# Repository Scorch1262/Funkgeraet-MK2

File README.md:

# Funkgeraet-MK2

Status:				Unfertig

Bezeichnung:			Funkgerät MK2

Auftragsnummer:			

Auftraggeber:			Privat

Designer:			Torben Bott

Beschreibung:			Funkgerät

				- Qi-Akku-Ladetechnik
				
				- ESP32 Steuerchip mit Bluetooth und WLAN
				
				- passend für DRA818U / DRA818V

Letzte Änderung:		10.05.2019	

Versorgungsspannung (Normal):	5V

Versorgungsspannung (Min.):	

Versorgungsspannung (Max.):	

Interne Spannungen:		5V / 3,7V

Frequenz: 			

Prozessor:			ESP32

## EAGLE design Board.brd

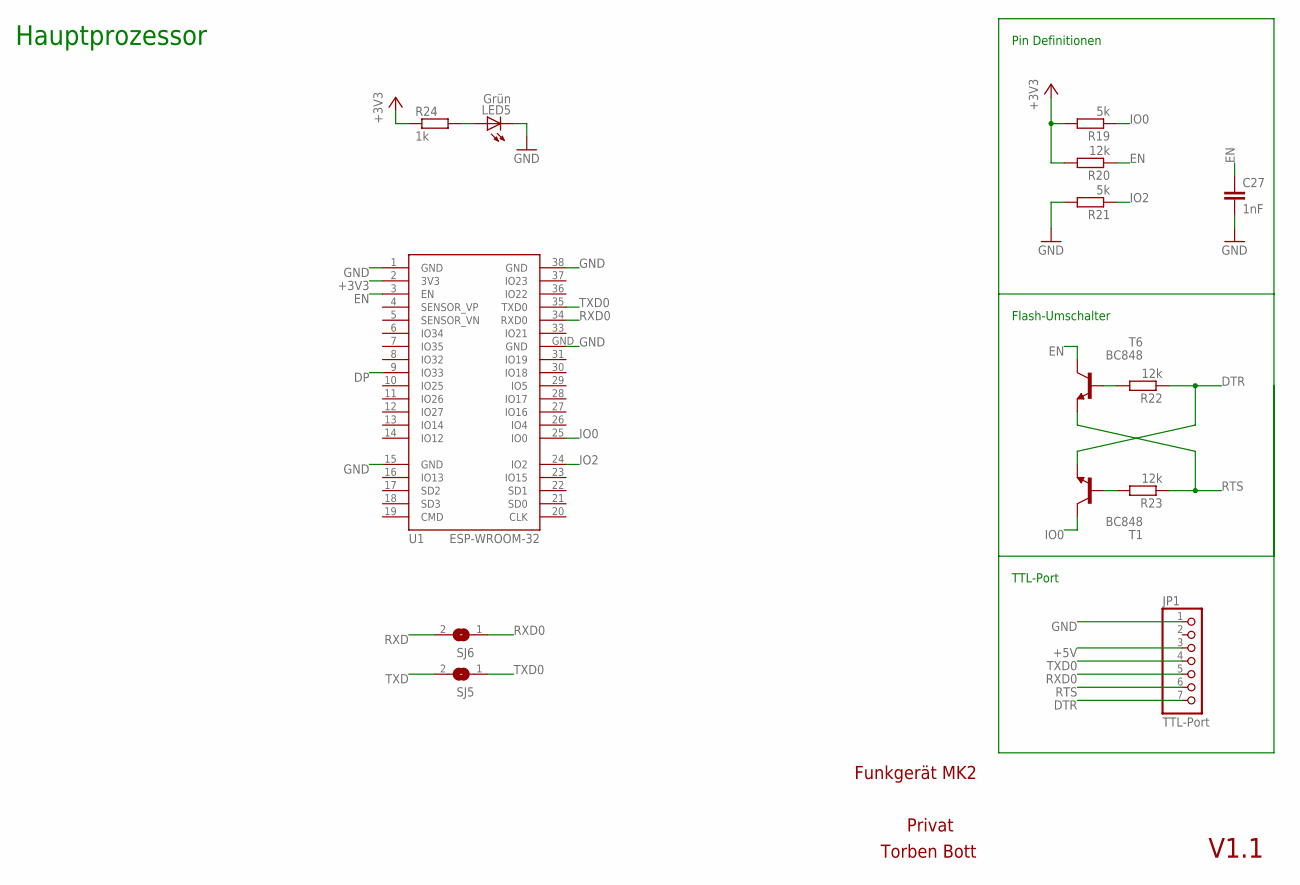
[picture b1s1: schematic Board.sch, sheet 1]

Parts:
C27: 1nF; C0805
JP1: TTL-Port; 1X07/90
LED5: Grün; CHIP-LED0805
R19, R21: 5k; R0805
R20, R22, R23: 12k; R0805
R24: 1k; R0805
SJ5, SJ6: SJ
T1, T6: BC848; SOT23
U1: ESP-WROOM-32

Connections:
+3V3: R19.2, R20.2, R24.1, U1.2 (3V3); also elsewhere on the board
+5V: JP1.3; also elsewhere on the board
DP: U1.9 (IO33); also elsewhere on the board
DTR: JP1.7, R22.1, T1.2 (E)
EN: C27.1, R20.1, T6.3 (C), U1.3 (EN)
GND: C27.2, JP1.1, LED5.C, R21.2, U1.1 (GND), U1.15 (GND), U1.38 (GND), U1.GND; also elsewhere on the board
IO0: R19.1, T1.3 (C), U1.25 (IO0)
IO2: R21.1, U1.24 (IO2)
unnamed: R23.2, T1.1 (B)
unnamed: R22.2, T6.1 (B)
unnamed: LED5.A, R24.2
RTS: JP1.6, R23.1, T6.2 (E)
RXD: SJ6.2; also elsewhere on the board
RXD0: JP1.5, SJ6.1, U1.34 (RXD0)
TXD: SJ5.2; also elsewhere on the board
TXD0: JP1.4, SJ5.1, U1.35 (TXD0)

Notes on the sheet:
Pin Definitionen
Flash-Umschalter
Funkgerät MK2
Privat
Torben Bott
V1.1
Hauptprozessor
TTL-Port

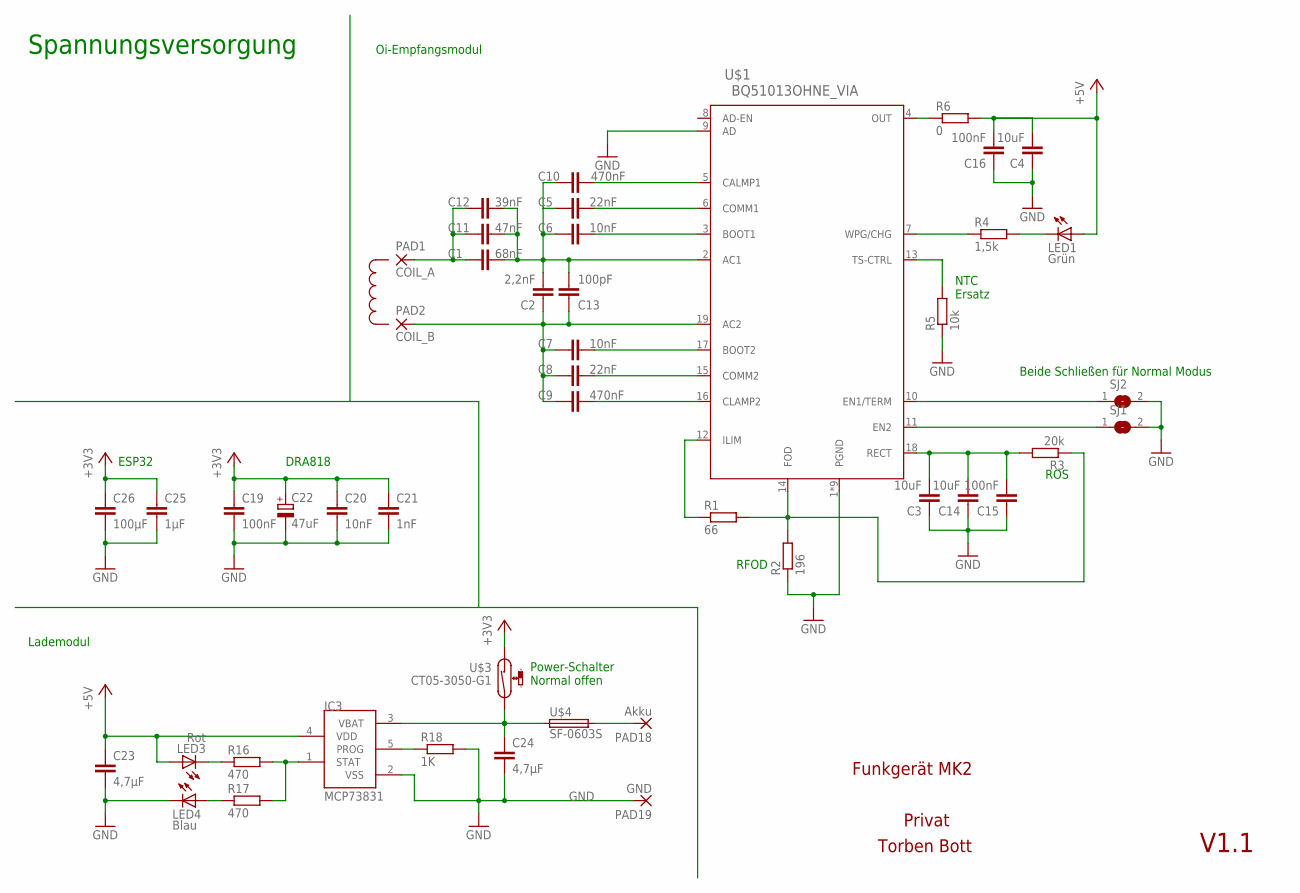
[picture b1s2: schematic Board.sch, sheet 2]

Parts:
C1: 68nF; C0805
C2: 2,2nF; C0805
C3, C4, C14: 10uF; C0805
C5, C8: 22nF; C0805
C6, C7, C20: 10nF; C0805
C9, C10: 470nF; C0805
C11: 47nF; C0805
C12: 39nF; C0805
C13: 100pF; C0805
C15, C16, C19: 100nF; C0805
C21: 1nF; C0805
C22: 47uF; CT6032
C23, C24: 4,7µF; C0805
C25: 1µF; C0805
C26: 100µF; C0805
IC3: MCP73831; SOT23-5L
LED1: Grün; CHIP-LED0805
LED3: Rot; CHIPLED_0805
LED4: Blau; CHIPLED_0805
PAD1: COIL_A; 5-2,5
PAD2: COIL_B; 5-2,5
PAD18: Akku; 5-1,8
PAD19: GND; 5-1,8
R1: 66; R0805
R2: 196; R0805
R3: 20k; R0805
R4: 1,5k; R0805
R5: 10k; R0805
R6: 0; R0805
R16, R17: 470; R0805
R18: 1K; R0805
SJ1, SJ2: SJ
U$1: BQ51013OHNE_VIA; QFN20_3,5X4,5_OHNE
U$3: CT05-3050-G1; CT10-A2
U$4: SF-0603S; R0603

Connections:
+3V3: C19.1, C20.1, C21.1, C22.+, C25.1, C26.1, U$3.P$1 (1); also elsewhere on the board
+5V: C4.2, C16.2, C23.1, IC3.4 (VDD), LED1.A, LED3.A, R6.2; also elsewhere on the board
BATT+: C24.1, IC3.3 (VBAT), U$3.P$2 (2), U$4.1
GND: C3.1, C4.1, C14.1, C15.1, C16.1, C19.2, C20.2, C21.2, C22.-, C23.2, C24.2, C25.2, C26.2, IC3.2 (VSS), LED4.C, PAD19.1, R2.1, R5.1, R18.2, SJ1.2, SJ2.2, U$1.1 (PGND), U$1.9 (AD), U$1.20 (PGND), U$1.EXP (PGND), U$1.EXP@7 (PGND), U$1.EXP@8 (PGND), U$1.EXP@9 (PGND), U$1.EXP@10 (PGND), U$1.EXP@11 (PGND), U$1.EXP@12 (PGND); also elsewhere on the board
unnamed: C1.1, C11.1, C12.1, PAD1.1
unnamed: C10.1, U$1.5 (CALMP1)
unnamed: C5.1, U$1.6 (COMM1)
unnamed: C1.2, C2.2, C5.2, C6.2, C10.2, C11.2, C12.2, C13.2, U$1.2 (AC1)
unnamed: C7.1, U$1.17 (BOOT2)
unnamed: C2.1, C7.2, C8.2, C9.2, C13.1, PAD2.1, U$1.19 (AC2)
unnamed: C8.1, U$1.15 (COMM2)
unnamed: C9.1, U$1.16 (CLAMP2)
unnamed: C6.1, U$1.3 (BOOT1)
unnamed: R1.1, U$1.12 (ILIM)
unnamed: PAD18.1, U$4.2
unnamed: C3.2, C14.2, C15.2, R3.2, U$1.18 (RECT)
unnamed: SJ2.1, U$1.10 (EN1/TERM)
unnamed: LED1.C, R4.2
unnamed: R6.1, U$1.4 (OUT)
unnamed: R4.1, U$1.7 (WPG/CHG)
unnamed: R5.2, U$1.13 (TS-CTRL)
unnamed: SJ1.1, U$1.11 (EN2)
unnamed: IC3.1 (STAT), R16.2, R17.2
unnamed: LED3.C, R16.1
unnamed: LED4.A, R17.1
unnamed: IC3.5 (PROG), R18.1
unnamed: R1.2, R2.2, R3.1, U$1.14 (FOD)

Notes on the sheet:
Funkgerät MK2
Privat
Torben Bott
V1.1
RFOD
ROS
NTC Ersatz
Beide Schließen für Normal Modus
Oi-Empfangsmodul
Lademodul
Spannungsversorgung
DRA818
ESP32
Power-Schalter Normal offen

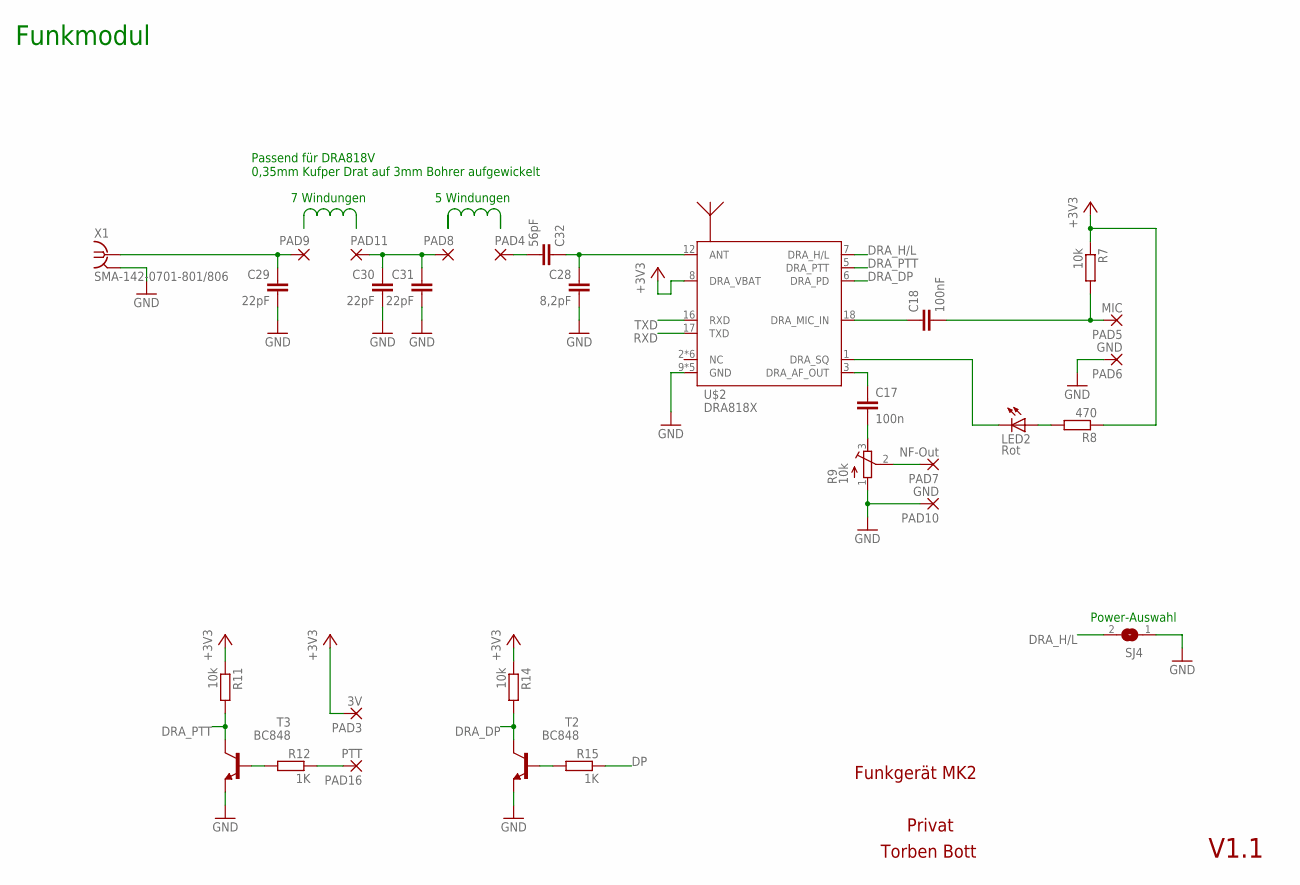
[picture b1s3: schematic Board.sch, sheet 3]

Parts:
C17: 100n; C0805
C18: 100nF; C0805
C28: 8,2pF; C1206K
C29, C30, C31: 22pF; C1206K
C32: 56pF; C1206K
LED2: Rot; CHIP-LED0805
PAD3: 3V; 5-1,8
PAD4, PAD8, PAD9, PAD11: WIREPADSMD5-1,8; 5-1,8
PAD5: MIC; 5-1,8
PAD6, PAD10: GND; 5-1,8
PAD7: NF-Out; 5-1,8
PAD16: PTT; 5-1,8
R7, R11, R14: 10k; R0805
R8: 470; R0805
R9: 10k; RTRIMTS63Y
R12, R15: 1K; R0805
SJ4: SJ
T2, T3: BC848; SOT23
U$2: DRA818X
X1: SMA-142-0701-801/806; J502-ND-142-0701-801/806

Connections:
+3V3: PAD3.1, R7.1, R8.1, R11.1, R14.1, U$2.8 (DRA_VBAT); also elsewhere on the board
DP: R15.1; also elsewhere on the board
DRA_DP: R14.2, T2.3 (C), U$2.6 (DRA_PD)
DRA_H/L: SJ4.2, U$2.7 (DRA_H/L)
DRA_PTT: R11.2, T3.3 (C), U$2.5 (DRA_PTT)
GND: C28.2, C29.2, C30.2, C31.2, PAD6.1, PAD10.1, R9.1 (A), SJ4.1, T2.2 (E), T3.2 (E), U$2.9 (GND), U$2.10 (GND), U$2.P1 (GND), U$2.P2 (GND), U$2.P3 (GND), X1.G@1 (2), X1.G@2 (2), X1.G@3 (2), X1.G@4 (2); also elsewhere on the board
unnamed: C18.1, U$2.18 (DRA_MIC_IN)
unnamed: C18.2, PAD5.1, R7.2
unnamed: LED2.A, R8.2
unnamed: C17.1, U$2.3 (DRA_AF_OUT)
unnamed: C17.2, R9.3 (E)
unnamed: C28.1, C32.1, U$2.12 (ANT)
unnamed: PAD7.1, R9.2 (S)
unnamed: C32.2, PAD4.1
unnamed: C30.1, C31.1, PAD8.1, PAD11.1
unnamed: LED2.C, U$2.1 (DRA_SQ)
unnamed: R12.2, T3.1 (B)
unnamed: C29.1, PAD9.1, X1.1
unnamed: R15.2, T2.1 (B)
unnamed: PAD16.1, R12.1
RXD: U$2.17 (TXD); also elsewhere on the board
TXD: U$2.16 (RXD); also elsewhere on the board

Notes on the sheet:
Power-Auswahl
Funkgerät MK2
Privat
Torben Bott
V1.1
Funkmodul
7 Windungen
5 Windungen
Passend für DRA818V 0,35mm Kufper Drat auf 3mm Bohrer aufgewickelt

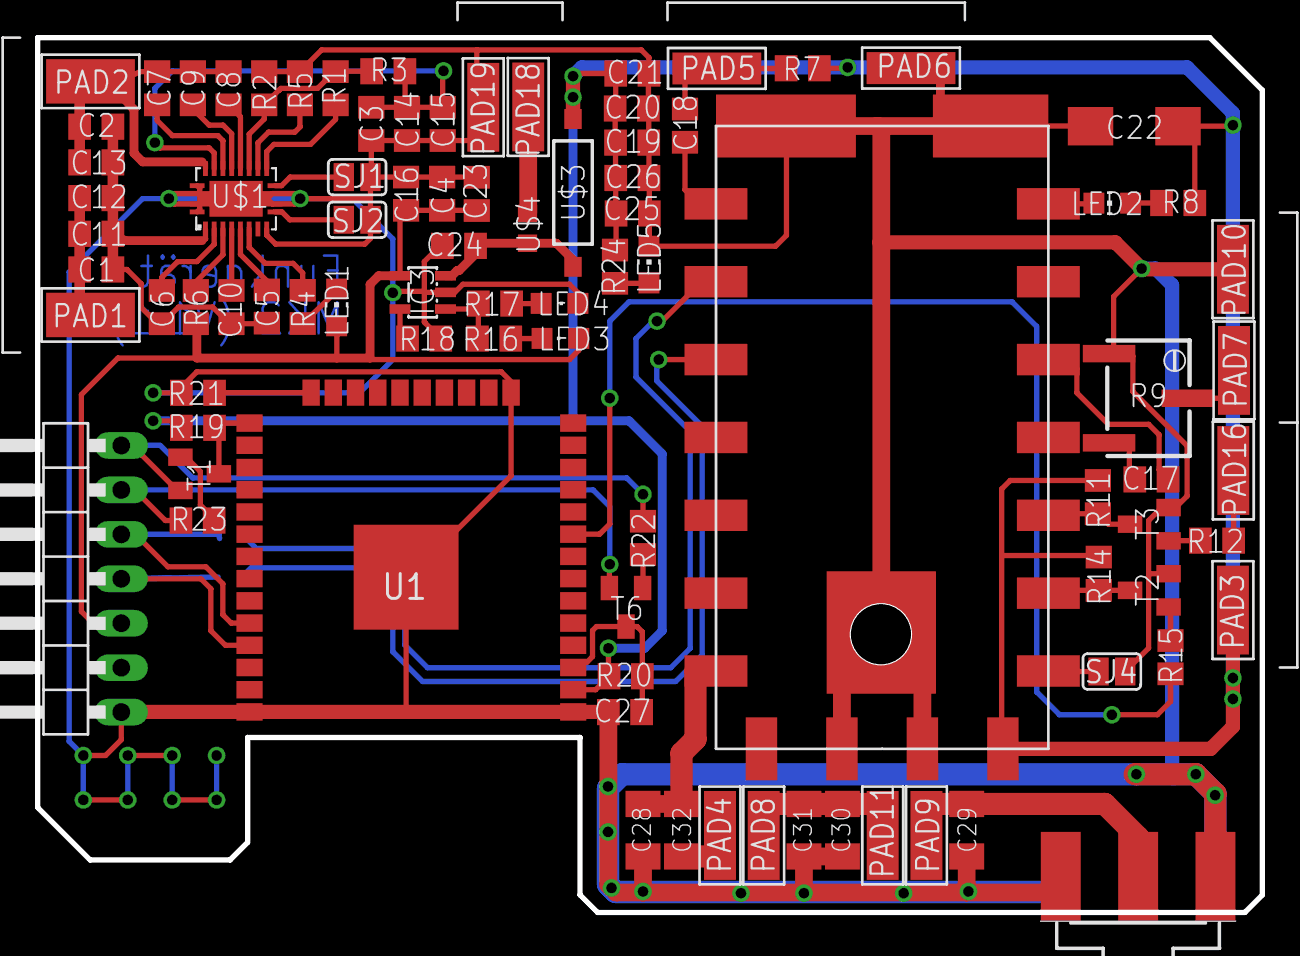
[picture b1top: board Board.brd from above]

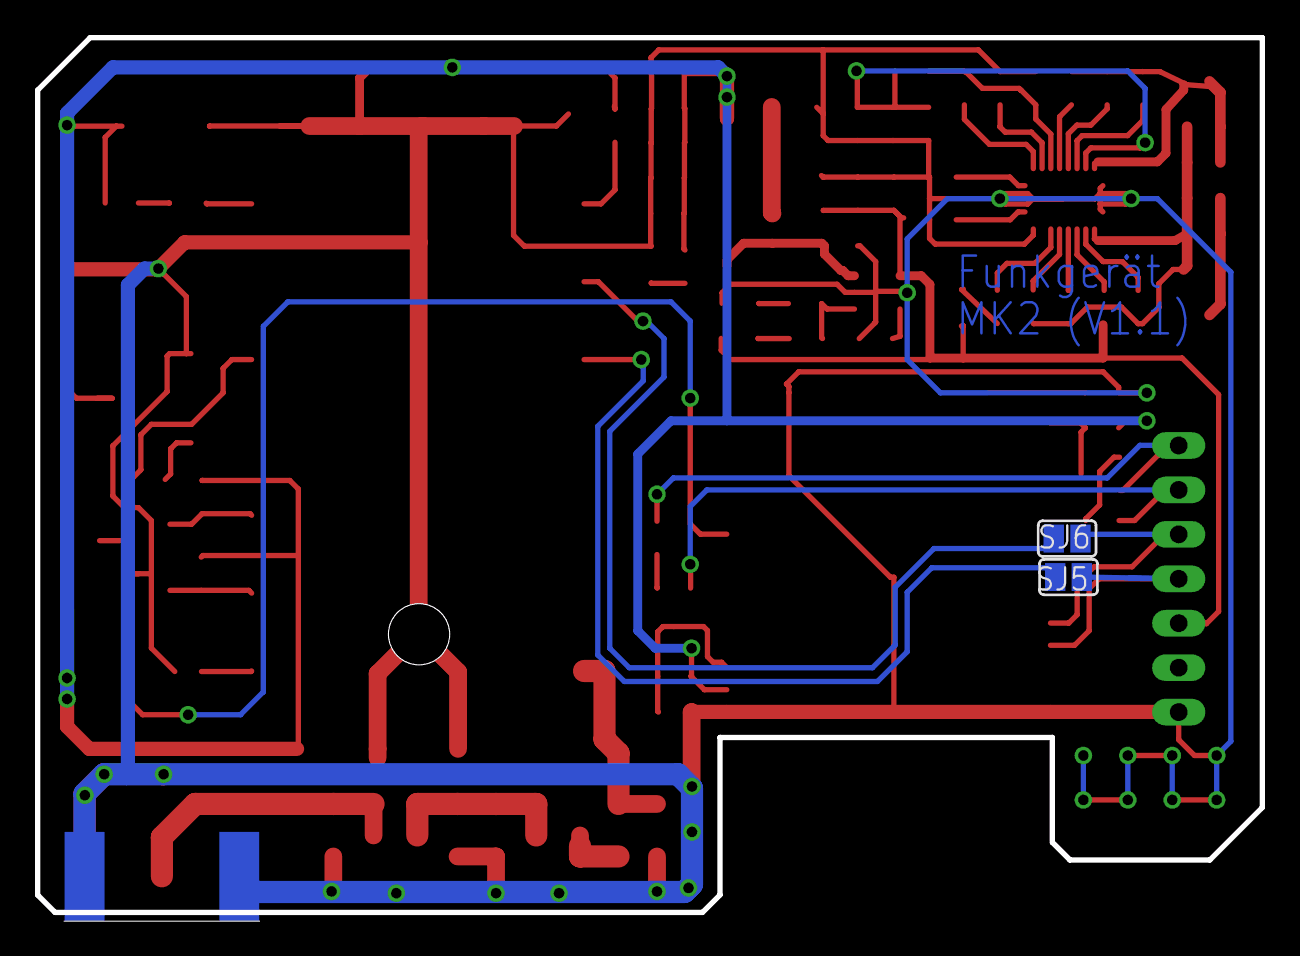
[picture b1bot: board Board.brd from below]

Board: 2 copper layers, 70.0 x 50.3 mm, 90 parts (2 on the bottom side), 57 nets.

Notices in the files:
parts and their libraries:
esp32: Creative Commons Attribution-ShareAlike 4.0 International
